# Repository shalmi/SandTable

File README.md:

# SandTable
Build a Table based on the Sisyphus Table

## TODO:
- [x] Build R-Axis
- [ ] Build Theta Axis
- [ ] Documentation
- [ ] Consider Trinamic Drivers
- [ ] Consider Making my own board rather than using Ramps (good experience)
- [ ] Build Table

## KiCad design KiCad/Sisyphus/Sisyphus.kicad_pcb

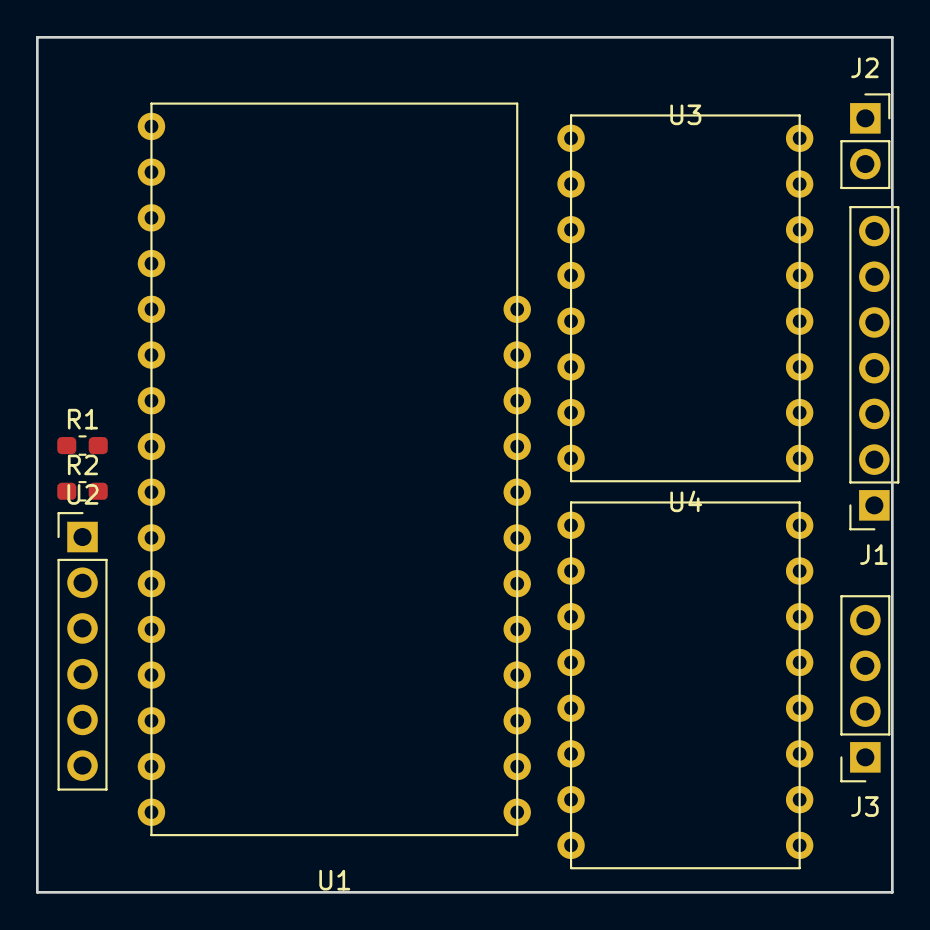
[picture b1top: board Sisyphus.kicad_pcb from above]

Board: 2 copper layers, 47.5 x 47.5 mm, 9 parts (0 on the bottom side), 24 nets, no tracks yet.

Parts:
J1: Conn_01x07_Male; PinSocket_1x07_P2.54mm_Vertical
J2: Conn_01x02_Male; PinSocket_1x02_P2.54mm_Vertical
J3: Conn_01x04_Male; PinSocket_1x04_P2.54mm_Vertical
R1, R2: 2K; R_0603_1608Metric_Pad1.05x0.95mm_HandSolder
U1: HUZZAH32; Huzzah32_Footprint
U2: MicroSD_Card_Adapter; PinHeader_1x06_P2.54mm_Vertical
U3, U4: TMC2130_Breakout; TMC_2130_Footprint

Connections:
3V: U1.2, U3.2, U4.2
21: U1.16, U3.9
A3_39: J1.2, R1.2, U1.8
A4_36: J1.3, R2.2, U1.9
A5_4: U1.10, U2.1
A6_14: U1.19, U4.16
A7_32: U1.20, U4.15
A8_15: U1.21, U4.9
A9_33: U1.22, U3.15
A10_27: U1.23, U3.16
GND: J1.1, J2.2, R1.1, R2.1, U1.4, U2.6, U3.1, U3.7, U4.1, U4.7
High_Motor_Voltage: J2.1, U3.8, U4.8
MISO_19: U1.13, U2.4
MOSI_18: U1.12, U2.3
Radius_Motor_A: J3.1, U4.3
Radius_Motor_B: J3.2, U4.4
Radius_Motor_C: J3.3, U4.5
Radius_Motor_D: J3.4, U4.6
SCK_5: U1.11, U2.2
Theta_Motor_A: J1.4, U3.3
Theta_Motor_B: J1.5, U3.4
Theta_Motor_C: J1.6, U3.5
Theta_Motor_D: J1.7, U3.6
USB_5V: U1.26, U2.5

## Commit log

2018-06-02 initial commit with lots of stuff. Working Simulator in Processing and Motors working with ramps board in arduino
2018-06-26 testingCode added. makes the box go back and forth hitting switches
2018-06-27 Lots of changes here:
    I removed a ton of files
    cleaned the workspace
    tried to add some cpp and h files
    using htem to hopefully get classes and objects working
2018-06-27 made some changes. Still havent tested them yet.
2018-06-28 got a few more basics layed out. Found simple timer.. it could solve the Stepper update issue I was concerned w/
2018-06-28 testing ReadMe changes
2018-07-03 some basic TMC2130 work and some lil upgrades
2018-07-03 working on state machine for calibrating on startup
2018-07-03 oh you know..just breaking some stuff while reorganizing again
2018-07-03 seperated further into classes. In a working state as of right now.
2018-07-03 Calibration works and then allows you to type in a desired Step to go to
2018-07-04 steps to mm comment
2018-07-04 testing adding readme file made other changes. trinamics are quieter with no config currently suck when i configure them...what the hell
2018-07-04 video on readme
2018-07-04 missing space
2018-07-05 adding thetaArm...this does NOT work yet
2018-07-18 Fixed compilation errors on ThetaArm. Also made the Constants private in the header. This was done for both radiusarm and thetaarm
2018-07-19 adding a comment
2018-07-20 Got both motors working at the same time. now need to get thier hz right
2018-07-20 This should allow both Steppers to work at different Hz Has not been tested yet but does compile
2018-07-20 fixed a missing line about midsteps
2018-07-20 better speeds
2018-07-22 wokring 2 motors at different speeds. also have 2 inputs and 2nd input is the theta angle in degrees
2018-07-23 currently finds the hall effect sensor but cant calibrate the 360 steps
2018-07-25 initial submission of DesignMaker
2018-07-25 updated with state machine. Also can semi detect outside loop
2018-07-25 added in sandify stuff
2018-07-26 made code to find interseciton points...what a pain in the behind
2018-07-27 getting gcode reader working ish
2018-07-28 getting the points outside of a circle to be replaced properly!
2018-07-28 more fixes. close but not quite done
2018-07-29 it works :) prolly still very breakable but it works
2018-07-30 update closer to working fully. still some issues
2018-07-31 i broke something :'(
2018-07-31 refixed and also slightly rebroken
2018-07-31 WORKING MORE :D
2018-07-31 updated processing scripts again
2018-08-13 added KiCad and some basic schematic stuff
2018-08-28 lots of updates.
2018-08-28 added a blank line
2018-08-28 small commit so I can work on this later
2018-08-28 some stuff that i need to delete if division and atan are as slow as i believe
2018-08-30 added ReadMe for new GCodeFenageler
2018-08-31 wrote this whole program and realized it is useless I cant easily draw lines on the table if only given polars...ugh
2018-08-31 making some changes to try and get the arduino to do some conversion from cartesian to polar
2018-08-31 Currently goes to cartesian coordinates based on 1000 grid center makes theta 0.thats bad
2018-09-03 THIS CODE IS BROKEN. It will be good later though :) starting to add stuff about going to major points one at a time
2018-09-06 added pointers in one spot...lets see if it breaks it lol. got some basic c++ code working. it should be a baseline to use to find minor points between major ones.
2018-09-06 Working and goes to multiple major points does not currently go in a straight line
2018-09-07 very jittery and needs to have theta go cleanly from 359 to 1 must code it to travel without going all the way back
2018-10-03 more points per distance. maybe try even more later it is still not great. maybe slow down the speed? also added points to make it go back and forth in a straight line
2018-10-04 made it MUCH slower and also a little better
2018-11-03 switched to Huzzah32 Feather adafruit board
2018-11-03 Disabling the motor was apparently the problem with the noise made some code to disable the motor if it hasnt been used in a while honestly im not sure how well it works though heat will be a problem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
2018-11-03 adding some json files for vscode
2018-11-06 some basic string parsing to consider in cpp to pull down the gcode.
2018-11-10 disabling steppers
2018-11-10 adding clearGit Script
2018-11-12 working with sd card. got it to work by using different examples some built for esp32 directly got it working but it has lots of quirks like: opening and closing files each time it reads not starting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
2018-11-12 added 2 cores to readme
2018-11-12 added ability to open a file, close a file, and read individual lines one at a time
2018-11-13 added code files I have tested seperately that need to work together sd card reading sd card parsing dual core work FIFO queues getting so close to being done here
2018-11-13 after much fiddling. multicore working with reading sd card and main loop problem had to do with the stack size the other core was getting
2018-11-13 seperated 2nd core into a seperate file. Also got a very basic FIFO queue working between the cores...SNAP!
2018-11-14 got queue working across files. created a gcodestruct to hold points that fits in the queue need to get queue to only parse to a limited size amount this would be to not run out of memory
2018-11-14 working on getting the code to keep a good queue at a good speed. currently cant start re reading old files. not sure why yet
2018-11-18 first design printed while read from card :D
2019-04-18 adding a bunch of kicad stuff and references!
2019-04-18 more kicad
